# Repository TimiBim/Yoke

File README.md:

# Yoke

A sim racing steering wheel / yoke controller built around an STM32G491VE.

## Overview

Yoke is a wheel-side controller for a sim racing rig. It handles button and
encoder input, drives a color touch display, and communicates with the base
over CAN bus. Power and data arrive over a single hot-pluggable connector.

## Features

- **STM32G491VE** (LQFP100, Cortex-M4F @ 170 MHz)
- **FDCAN** link to the wheel base via TCAN332G transceiver
- **ILI9341** 320×240 SPI touch display
- **MCP23017** I²C expander for button matrix
- **Hot-plug safe** — MIC2544 current-limit controller and charge pump so the
  wheel can be connected while the rig is powered
- **ESD protection** on all external connections (ESD2CAN24DCKRQ1)
- **USB-C** for firmware flashing and debug

## Power Architecture

The base supplies a 5 V intermediate rail. An AP2114H-3.3 LDO generates the
local 3.3 V rail on the wheel, keeping the connector current low and avoiding
drop across the cable.

## License

- Hardware: CERN-OHL-S v2
- Firmware: MIT

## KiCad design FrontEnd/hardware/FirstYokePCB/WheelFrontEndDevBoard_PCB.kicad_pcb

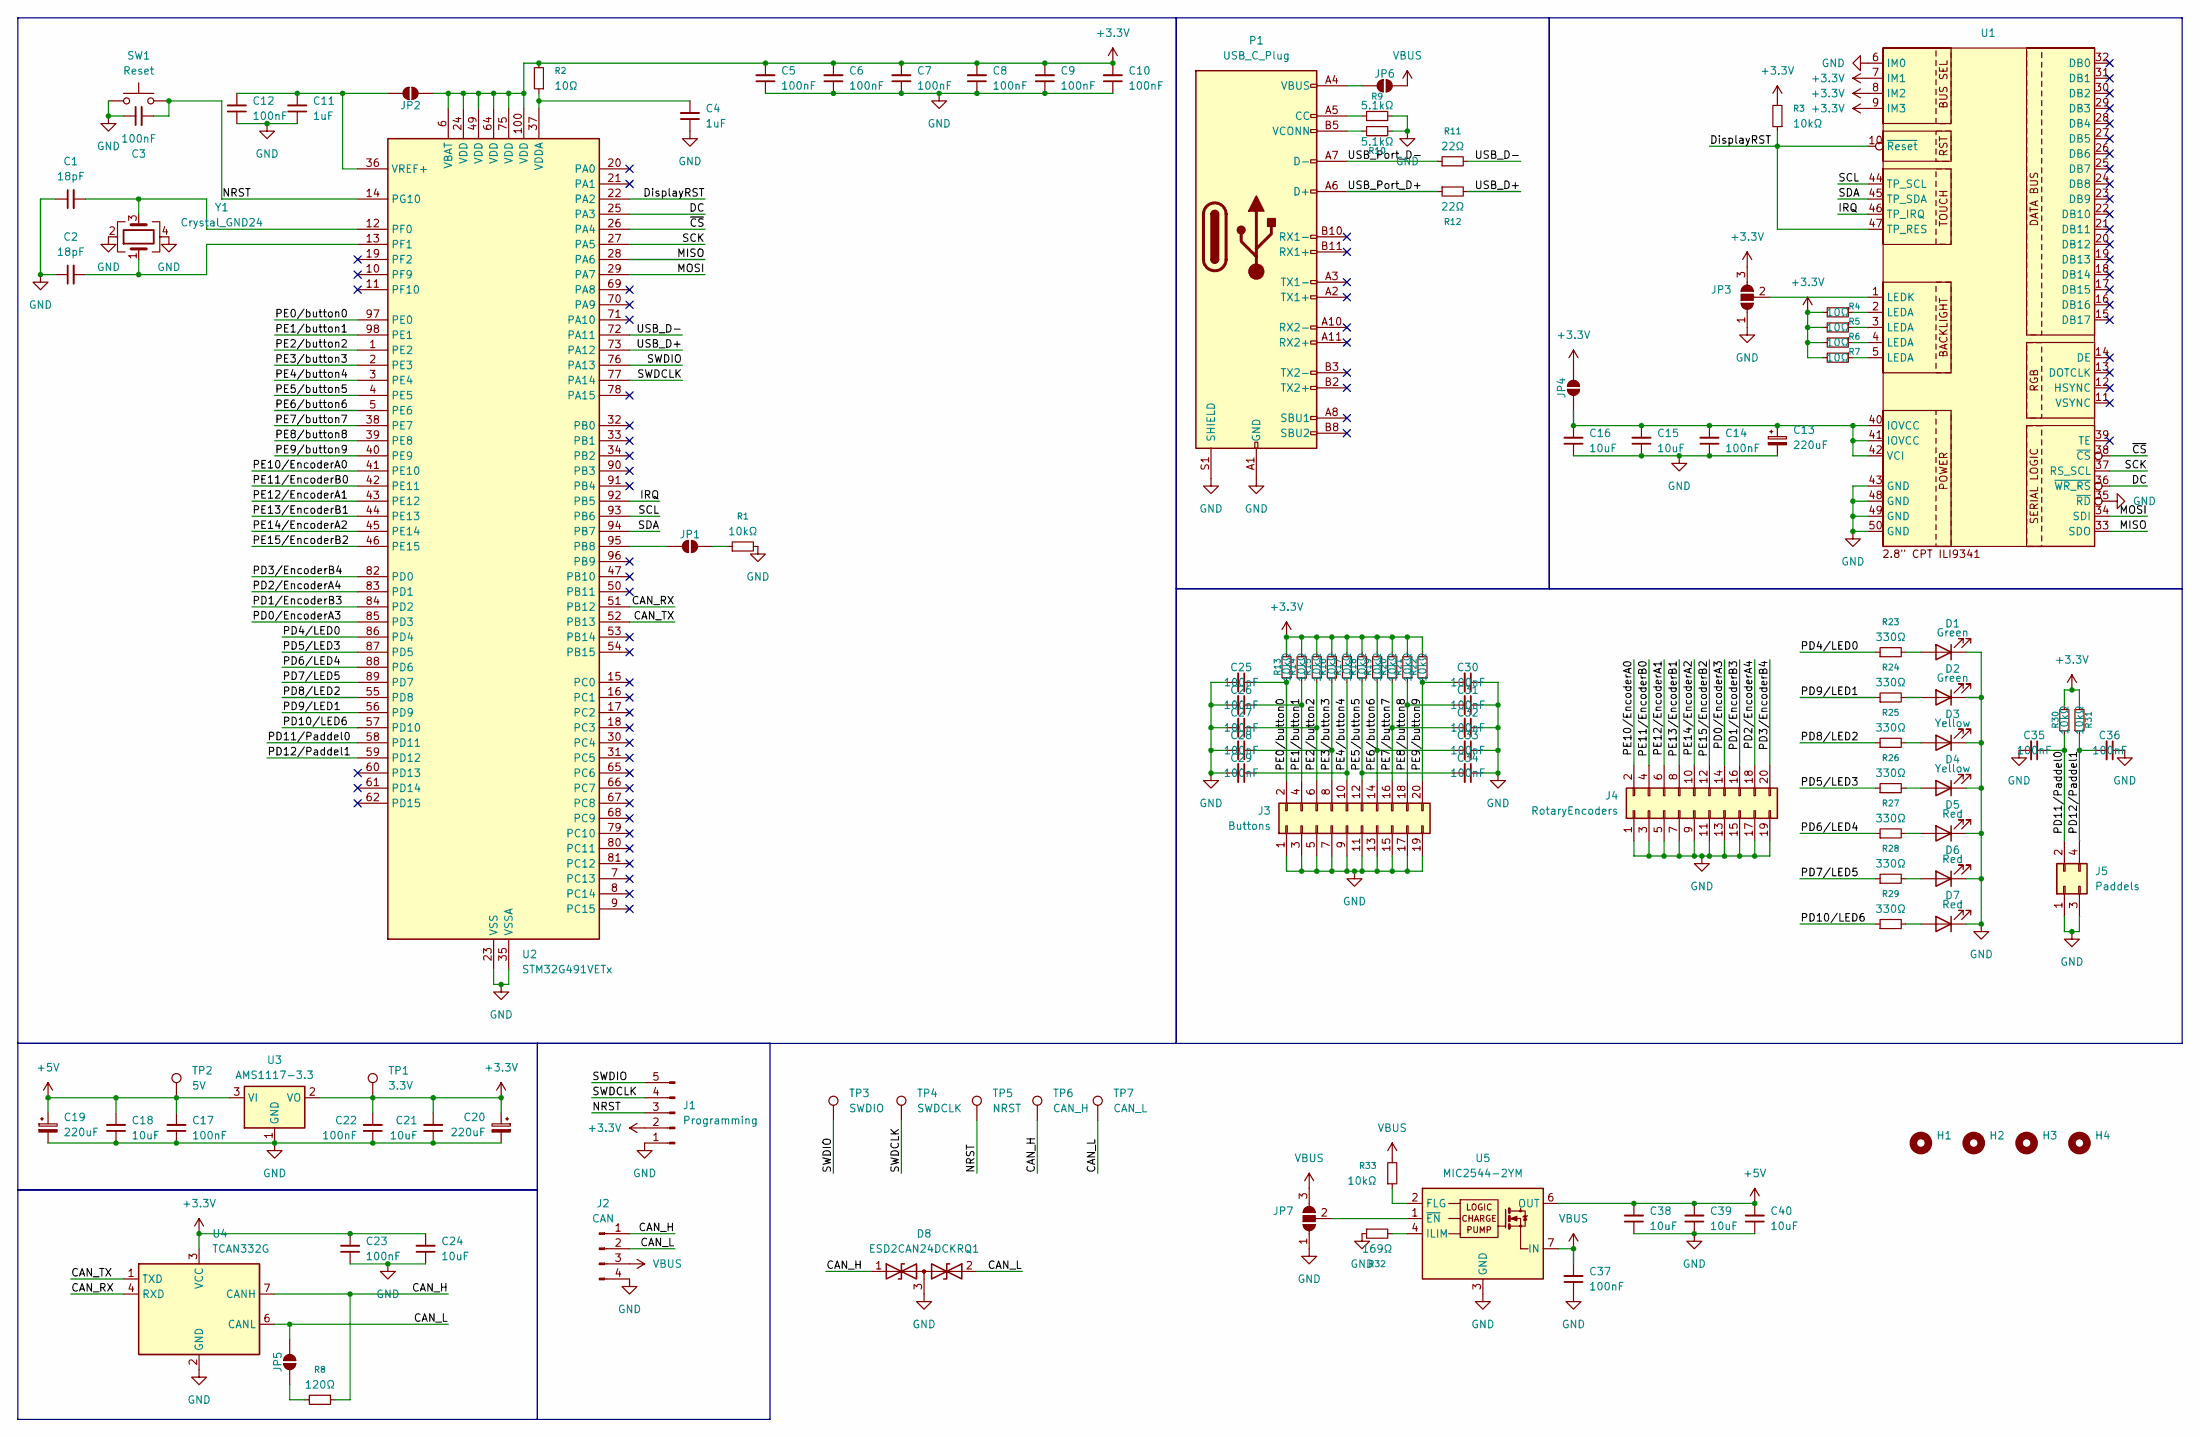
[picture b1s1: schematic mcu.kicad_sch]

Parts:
C1, C2: 18pF; C_0603_1608Metric_Pad1.08x0.95mm_HandSolder
C3, C5, C6, C7, C8, C9, C10, C12, C14, C17, C22, C23, C25, C26, C27, C28, C29, C30, C31, C32, C33, C34, C35, C36, C37: 100nF; C_0603_1608Metric_Pad1.08x0.95mm_HandSolder
C4, C11: 1uF; C_0603_1608Metric_Pad1.08x0.95mm_HandSolder
C13, C19, C20: 220uF; CP_Elec_6.3x5.3
C15, C16, C18, C21, C24, C38, C39, C40: 10uF; C_0603_1608Metric_Pad1.08x0.95mm_HandSolder
D1, D2: Green; LED_0603_1608Metric_Pad1.05x0.95mm_HandSolder
D3, D4: Yellow; LED_0603_1608Metric_Pad1.05x0.95mm_HandSolder
D5, D6, D7: Red; LED_0603_1608Metric_Pad1.05x0.95mm_HandSolder
D8: ESD2CAN24DCKRQ1; SOT-323_SC-70
H1, H2, H3, H4: MountingHole; MountingHole_3.2mm_M3
J1: Programming; PinHeader_1x05_P2.54mm_Vertical
J2: CAN; PinHeader_1x04_P2.54mm_Vertical
J3: Buttons; PinHeader_2x10_P2.54mm_Vertical
J4: RotaryEncoders; PinHeader_2x10_P2.54mm_Vertical
J5: Paddels; PinHeader_2x02_P2.54mm_Vertical
JP1, JP2, JP4, JP5, JP6: SolderJumper_2_Open; SolderJumper-2_P1.3mm_Open_RoundedPad1.0x1.5mm
JP3, JP7: SolderJumper_3_Open; SolderJumper-3_P1.3mm_Open_RoundedPad1.0x1.5mm
P1: USB_C_Plug; USB-C
R1, R3, R13, R14, R15, R16, R17, R18, R19, R20, R21, R22, R30, R31, R33: 10kΩ; R_0603_1608Metric_Pad0.98x0.95mm_HandSolder
R2, R4, R5, R6, R7: 10Ω; R_0603_1608Metric_Pad0.98x0.95mm_HandSolder
R8: 120Ω; R_0603_1608Metric_Pad0.98x0.95mm_HandSolder
R9, R10: 5.1kΩ; R_0603_1608Metric_Pad0.98x0.95mm_HandSolder
R11, R12: 22Ω; R_0603_1608Metric_Pad0.98x0.95mm_HandSolder
R23, R24, R25, R26, R27, R28, R29: 330Ω; R_0603_1608Metric_Pad0.98x0.95mm_HandSolder
R32: 169Ω; R_0603_1608Metric_Pad0.98x0.95mm_HandSolder
SW1: Reset; PTS815
TP1: 3.3V; TestPoint_Pad_D1.5mm
TP2: 5V; TestPoint_Pad_D1.5mm
TP3: SWDIO; TestPoint_Pad_D1.5mm
TP4: SWDCLK; TestPoint_Pad_D1.5mm
TP5: NRST; TestPoint_Pad_D1.5mm
TP6: CAN_H; TestPoint_Pad_D1.5mm
TP7: CAN_L; TestPoint_Pad_D1.5mm
U1: Adafruit 2.8_ capacitiveTouchScreen
U2: STM32G491VETx; LQFP-100_14x14mm_P0.5mm
U3: AMS1117-3.3; SOT-223-3_TabPin2
U4: TCAN332G; SOT-23-8_Handsoldering
U5: MIC2544-2YM; SOIC-8_3.9x4.9mm_P1.27mm
Y1: Crystal_GND24; ABM8G

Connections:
+3.3V: C5.2, C6.2, C7.2, C8.2, C9.2, C10.2, C20.1, C21.2, C22.2, C23.2, C24.2, J1.2, JP2.1 (A), JP3.3 (B), JP4.2 (B), R2.2, R3.2, R4.2, R5.2, R6.2, R7.2, R13.2, R14.2, R15.2, R16.2, R17.2, R18.2, R19.2, R20.2, R21.2, R22.2, R30.2, R31.2, TP1.1 (1_1), U1.7 (IM1), U1.8 (IM2), U1.9 (IM3), U2.6 (VBAT), U2.24 (VDD), U2.49 (VDD), U2.64 (VDD), U2.75 (VDD), U2.100 (VDD), U3.2 (VO), U4.3 (VCC)
+5V: C17.2, C18.2, C19.1, C38.2, C39.2, C40.2, TP2.1 (1_1), U3.3 (VI), U5.6 (OUT), U5.8 (OUT)
/MCU/CAN_H: D8.1 (A1), J2.1, R8.1, TP6.1 (1_1), U4.7 (CANH)
/MCU/CAN_L: D8.2 (A2), J2.2, JP5.2 (B), TP7.1 (1_1), U4.6 (CANL)
/MCU/CAN_RX: U2.51 (PB12), U4.4 (RXD)
/MCU/CAN_TX: U2.52 (PB13), U4.1 (TXD)
/MCU/DC: U1.36 (~WR_RS), U2.25 (PA3)
/MCU/DisplayRST: R3.1, U1.10 (~Reset), U1.47 (TP_RES), U2.22 (PA2)
/MCU/IRQ: U1.46 (TP_IRQ), U2.92 (PB5)
/MCU/MISO: U1.33 (SDO), U2.28 (PA6)
/MCU/MOSI: U1.34 (SDI), U2.29 (PA7)
/MCU/NRST: C3.2, J1.3, SW1.2, TP5.1 (1_1), U2.14 (PG10)
/MCU/PD0/EncoderA3: J4.14, U2.85 (PD3)
/MCU/PD1/EncoderB3: J4.16, U2.84 (PD2)
/MCU/PD2/EncoderA4: J4.18, U2.83 (PD1)
/MCU/PD3/EncoderB4: J4.20, U2.82 (PD0)
/MCU/PD4/LED0: R23.1, U2.86 (PD4)
/MCU/PD5/LED3: R26.1, U2.87 (PD5)
/MCU/PD6/LED4: R27.1, U2.88 (PD6)
/MCU/PD7/LED5: R28.1, U2.89 (PD7)
/MCU/PD8/LED2: R25.1, U2.55 (PD8)
/MCU/PD9/LED1: R24.1, U2.56 (PD9)
/MCU/PD10/LED6: R29.1, U2.57 (PD10)
/MCU/PD11/Paddel0: C35.1, J5.2, R30.1, U2.58 (PD11)
/MCU/PD12/Paddel1: C36.2, J5.4, R31.1, U2.59 (PD12)
/MCU/PE0/button0: C25.1, J3.2, R13.1, U2.97 (PE0)
/MCU/PE1/button1: C26.1, J3.4, R14.1, U2.98 (PE1)
/MCU/PE2/button2: C27.1, J3.6, R15.1, U2.1 (PE2)
/MCU/PE3/button3: C28.1, J3.8, R16.1, U2.2 (PE3)
/MCU/PE4/button4: C29.1, J3.10, R17.1, U2.3 (PE4)
/MCU/PE5/button5: C34.2, J3.12, R18.1, U2.4 (PE5)
/MCU/PE6/button6: C33.2, J3.14, R19.1, U2.5 (PE6)
/MCU/PE7/button7: C32.2, J3.16, R20.1, U2.38 (PE7)
/MCU/PE8/button8: C31.2, J3.18, R21.1, U2.39 (PE8)
/MCU/PE9/button9: C30.2, J3.20, R22.1, U2.40 (PE9)
/MCU/PE10/EncoderA0: J4.2, U2.41 (PE10)
/MCU/PE11/EncoderB0: J4.4, U2.42 (PE11)
/MCU/PE12/EncoderA1: J4.6, U2.43 (PE12)
/MCU/PE13/EncoderB1: J4.8, U2.44 (PE13)
/MCU/PE14/EncoderA2: J4.10, U2.45 (PE14)
/MCU/PE15/EncoderB2: J4.12, U2.46 (PE15)
/MCU/SCK: U1.37 (RS_SCL), U2.27 (PA5)
/MCU/SCL: U1.44 (TP_SCL), U2.93 (PB6)
/MCU/SDA: U1.45 (TP_SDA), U2.94 (PB7)
/MCU/SWDCLK: J1.4, TP4.1 (1_1), U2.77 (PA14)
/MCU/SWDIO: J1.5, TP3.1 (1_1), U2.76 (PA13)
/MCU/USB_D+: R12.2, U2.73 (PA12)
/MCU/USB_D-: R11.2, U2.72 (PA11)
/MCU/USB_Port_D+: P1.A6 (D+), R12.1
/MCU/USB_Port_D-: P1.A7 (D-), R11.1
/MCU/~CS: U1.38 (~CS), U2.26 (PA4)
GND: C1.1, C2.1, C3.1, C4.1, C5.1, C6.1, C7.1, C8.1, C9.1, C10.1, C11.1, C12.1, C13.2, C14.1, C15.1, C16.1, C17.1, C18.1, C19.2, C20.2, C21.1, C22.1, C23.1, C24.1, C25.2, C26.2, C27.2, C28.2, C29.2, C30.1, C31.1, C32.1, C33.1, C34.1, C35.2, C36.1, C37.1, C38.1, C39.1, C40.1, D1.1 (K), D2.1 (K), D3.1 (K), D4.1 (K), D5.1 (K), D6.1 (K), D7.1 (K), D8.3 (common), J1.1, J2.4, J3.1, J3.3, J3.5, J3.7, J3.9, J3.11, J3.13, J3.15, J3.17, J3.19, J4.1, J4.3, J4.5, J4.7, J4.9, J4.11, J4.13, J4.15, J4.17, J4.19, J5.1, J5.3, JP3.1 (A), JP7.1 (A), P1.A1 (GND), P1.A12 (GND), P1.B1 (GND), P1.B12 (GND), P1.S1 (SHIELD), R1.2, R9.2, R10.2, R32.1, SW1.1, U1.6 (IM0), U1.35 (~RD), U1.43 (GND), U1.48 (GND), U1.49 (GND), U1.50 (GND), U2.23 (VSS), U2.35 (VSSA), U2.48 (VSS), U2.63 (VSS), U2.74 (VSS), U2.99 (VSS), U3.1 (GND), U4.2 (GND), U5.3 (GND), Y1.2, Y1.4
unnamed: D1.2 (A), R23.2
unnamed: D2.2 (A), R24.2
unnamed: D3.2 (A), R25.2
unnamed: D4.2 (A), R26.2
unnamed: D5.2 (A), R27.2
unnamed: D6.2 (A), R28.2
unnamed: D7.2 (A), R29.2
unnamed: JP1.1 (A), U2.95 (PB8)
unnamed: JP1.2 (B), R1.1
unnamed: C11.2, C12.2, JP2.2 (B), U2.36 (VREF+)
unnamed: JP3.2 (C), U1.1 (LEDK)
unnamed: C13.1, C14.2, C15.2, C16.2, JP4.1 (A), U1.40 (IOVCC), U1.41 (IOVCC), U1.42 (VCI)
unnamed: JP5.1 (A), R8.2
unnamed: JP6.1 (A), P1.A4 (VBUS), P1.A9 (VBUS), P1.B4 (VBUS), P1.B9 (VBUS)
unnamed: JP7.2 (C), U5.1 (~EN)
unnamed: P1.A5 (CC), R9.1
unnamed: P1.B5 (VCONN), R10.1
unnamed: R4.1, U1.2 (LEDA)
unnamed: R5.1, U1.3 (LEDA)
unnamed: R6.1, U1.4 (LEDA)
unnamed: R7.1, U1.5 (LEDA)
unnamed: C1.2, U2.12 (PF0), Y1.3
unnamed: C2.2, U2.13 (PF1), Y1.1
unnamed: C4.2, R2.1, U2.37 (VDDA)
unnamed: R33.1, U5.2 (FLG)
unnamed: R32.2, U5.4 (ILIM)
VBUS: C37.2, J2.3, JP6.2 (B), JP7.3 (B), R33.2, U5.7 (IN)

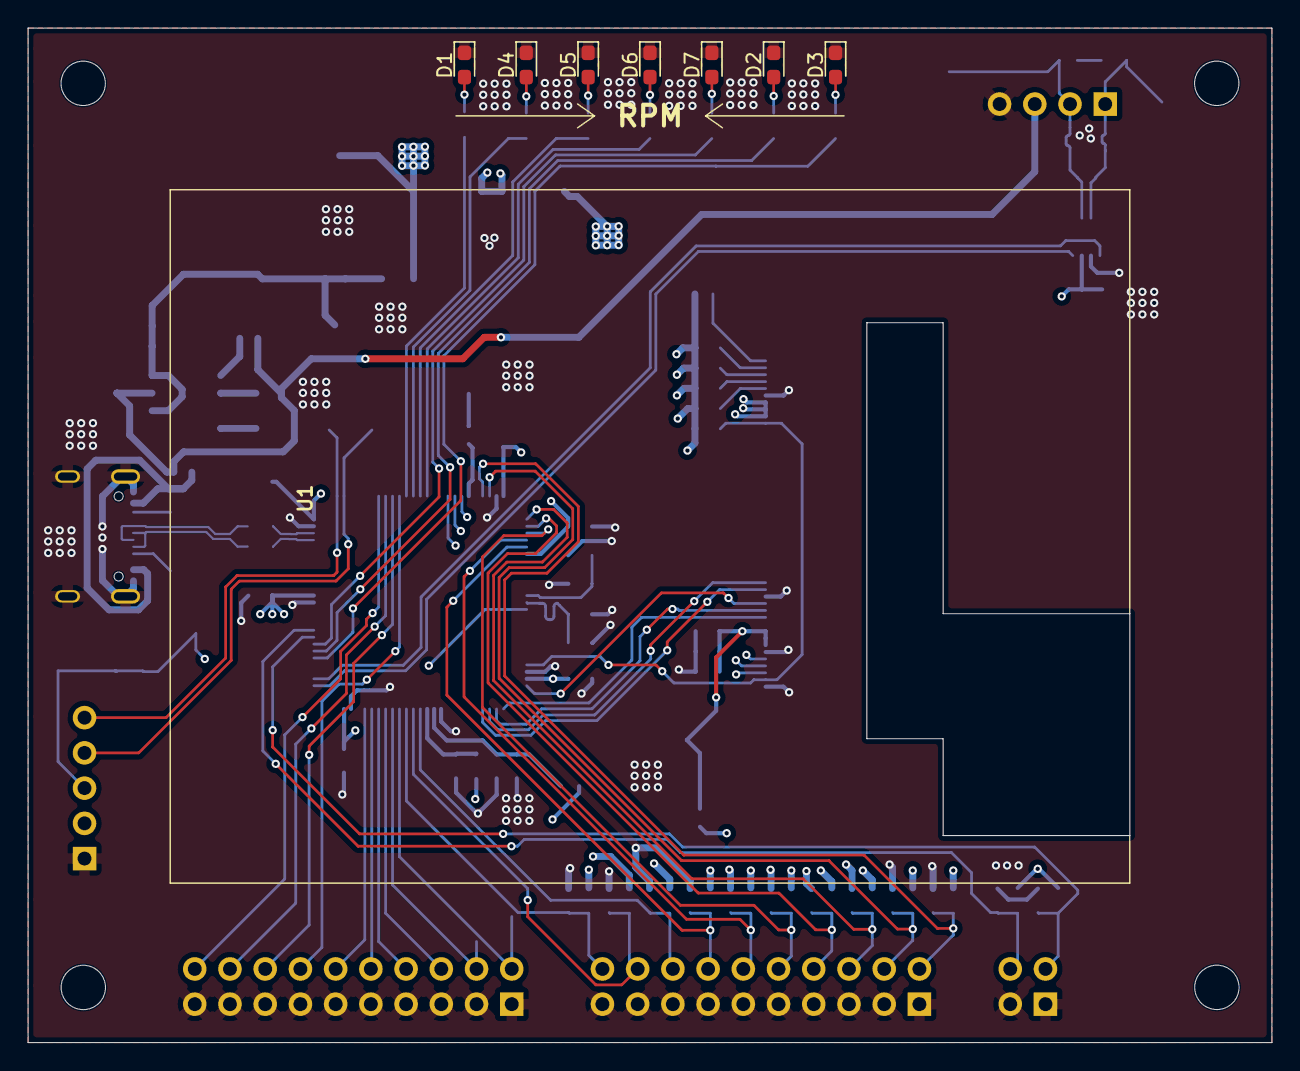
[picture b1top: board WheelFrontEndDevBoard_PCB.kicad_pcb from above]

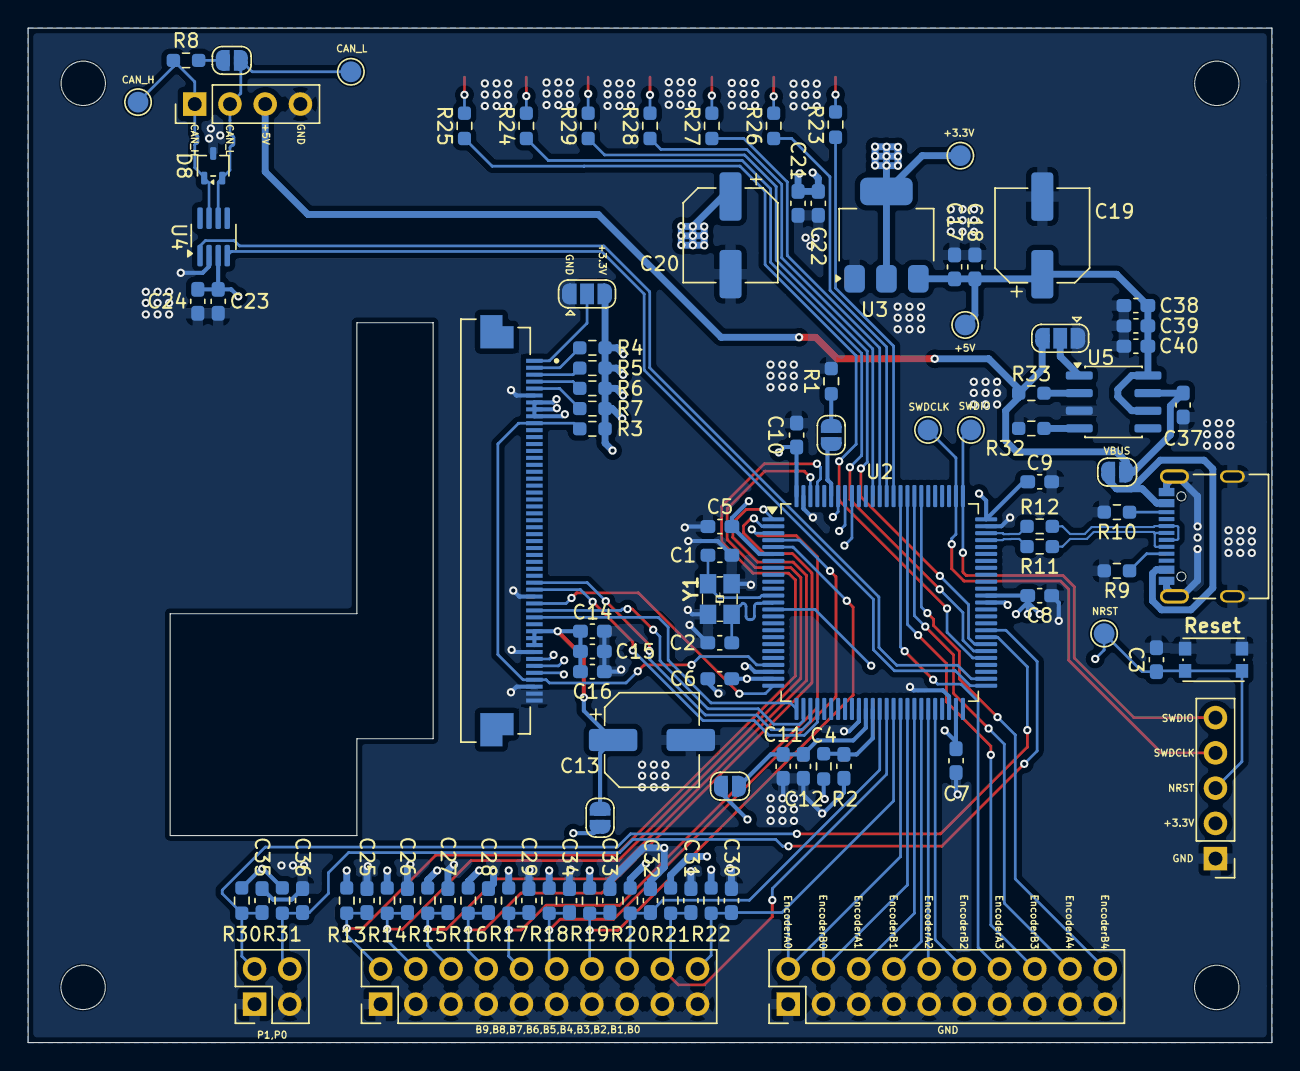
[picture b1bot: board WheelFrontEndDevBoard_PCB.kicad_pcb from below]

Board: 4 copper layers, 89.7 x 73.2 mm, 112 parts (100 on the bottom side), 79 nets.
